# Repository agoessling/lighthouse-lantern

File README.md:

lighthouse-lantern
==================

RGB LED pixel to be used with LightHouse.

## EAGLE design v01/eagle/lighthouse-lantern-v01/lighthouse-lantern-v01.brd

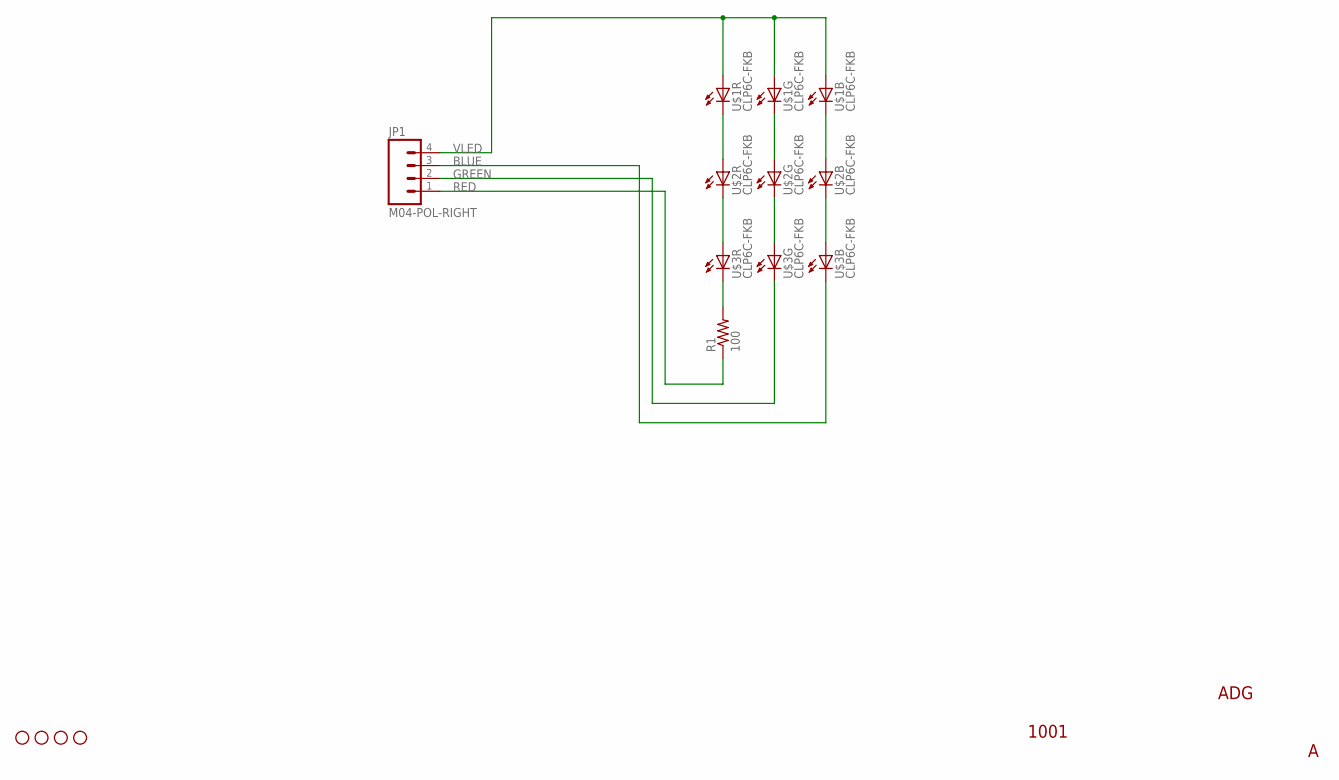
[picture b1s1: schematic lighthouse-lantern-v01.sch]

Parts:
JP1: M04-POL-RIGHT; 640455-4
JP2, JP3, JP4, JP5: STAND-OFF
R1: 100; R1206
U$1, U$2, U$3: CLP6C-FKB

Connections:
BLUE: JP1.3, U$3.4 (C)
GREEN: JP1.2, U$3.5 (C)
unnamed: U$1.6 (C), U$2.1 (A)
unnamed: U$1.5 (C), U$2.2 (A)
unnamed: U$1.4 (C), U$2.3 (A)
unnamed: U$2.4 (C), U$3.3 (A)
unnamed: U$2.5 (C), U$3.2 (A)
unnamed: U$2.6 (C), U$3.1 (A)
unnamed: R1.2, U$3.6 (C)
RED: JP1.1, R1.1
VLED: JP1.4, U$1.1 (A), U$1.2 (A), U$1.3 (A)

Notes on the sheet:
ADG
1001

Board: 2 copper layers, 9 parts (0 on the bottom side), 11 nets, no tracks yet.

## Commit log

2012-12-22 Added GITIGNORE and README
2012-12-22 readme test
2012-12-22 Initial Push
2012-12-22 Added Insert Tool, Renamed Fab Docs, added Schem Doc

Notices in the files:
parts and their libraries:
SparkFun-Electromechanical: Licensing: CC v3.0 Share-Alike You are welcome to use this library for commercial purposes.
